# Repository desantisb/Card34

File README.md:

# Card34
A compact split keyboard with 34 keys and bluetooth connection

Initial design is done starting from Sweep2.1 half design.

wiring is kept same as the sweep so Sweep compatible firmware should be also compatible with the Card34.

Card34 is supposed to work only through Bluetooth so TRRS connection has not been included.

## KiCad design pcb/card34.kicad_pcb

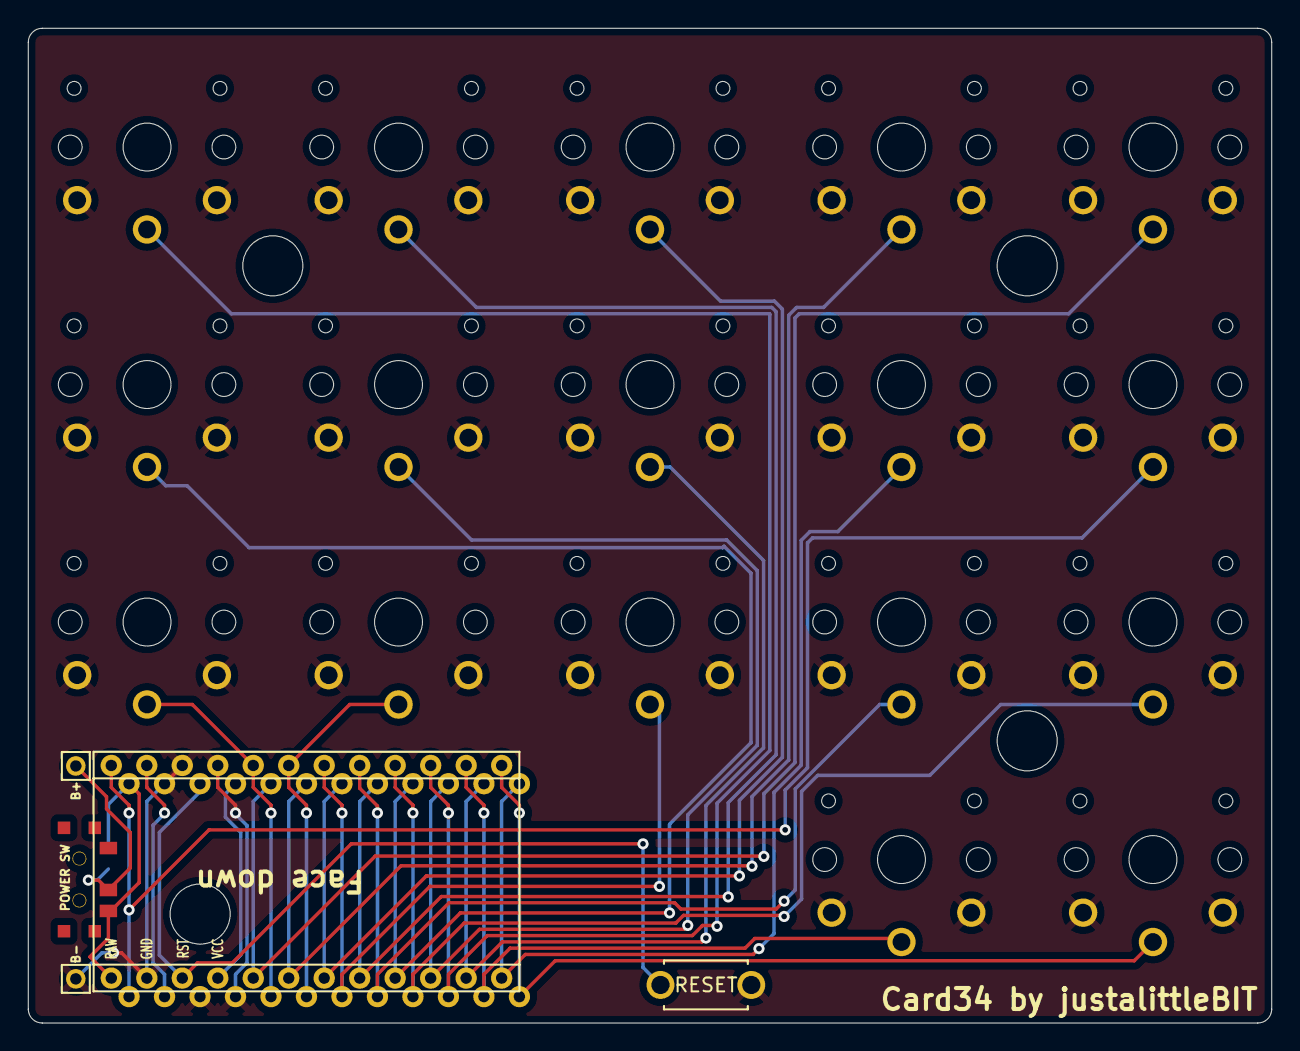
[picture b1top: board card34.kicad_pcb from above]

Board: 2 copper layers, 89.0 x 71.2 mm, 23 parts (1 on the bottom side), 21 nets.

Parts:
B+: MountingHole_Pad; 1pin_conn
B-: MountingHole_Pad; 1pin_conn
POWER SW: SW_SPDT; SPDT_C128955
RSW1: SW_Push; ResetSW
SW2, SW3, SW4, SW5, SW6, SW8, SW9, SW10, SW11, SW12, SW14, SW15, SW16, SW17, SW18, SW20, SW21: SW_Push; SW_PG1350_rev_DPB
SW2#2: SW_SPDT; SPDT_C128955r
U1: ProMicro-kbd; ProMicro_v2

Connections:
BT+_r: B+.1, POWER SW.2, SW2#2.2
Switch1: SW2.1, U1.10
Switch2: SW3.1, U1.17
Switch3: SW4.1, U1.18
Switch4: SW5.1, U1.19
Switch5: SW6.1, U1.20
Switch6: SW8.1, U1.16
Switch7: SW9.1, U1.15
Switch8: SW10.1, U1.14
Switch9: SW11.1, U1.13
Switch10: SW12.1, U1.1
Switch11: SW14.1, U1.5
Switch12: SW15.1, U1.6
Switch13: SW16.1, U1.7
Switch14: SW17.1, U1.8
Switch15: SW18.1, U1.9
Switch16: SW21.1, U1.11
Switch17: SW20.1, U1.12
gnd: B-.1, RSW1.1, SW2.2, SW3.2, SW4.2, SW5.2, SW6.2, SW8.2, SW9.2, SW10.2, SW11.2, SW12.2, SW14.2, SW15.2, SW16.2, SW17.2, SW18.2, SW20.2, SW21.2, U1.3, U1.4, U1.23
raw: POWER SW.3, SW2#2.3, U1.24
reset: RSW1.2, U1.22

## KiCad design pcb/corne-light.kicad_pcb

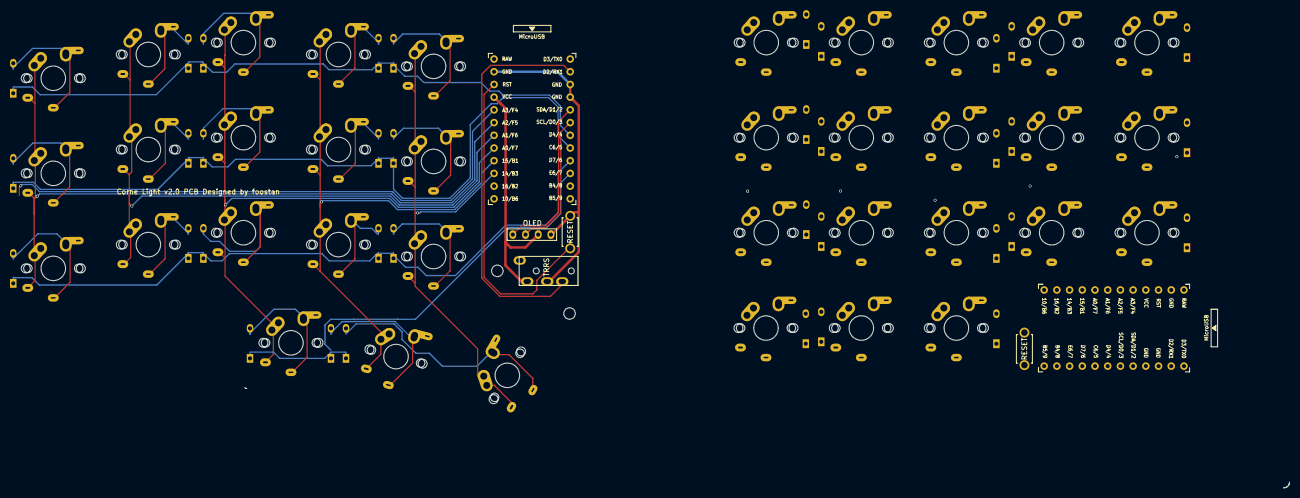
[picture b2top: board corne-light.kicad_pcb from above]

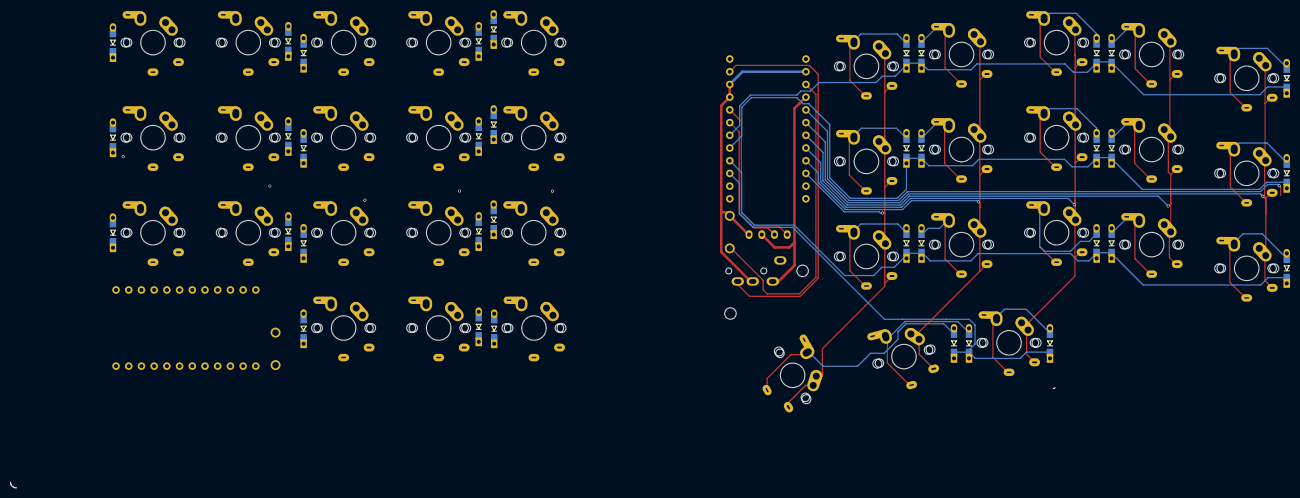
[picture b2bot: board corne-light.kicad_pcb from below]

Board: 2 copper layers, 80 parts (38 on the bottom side), 62 nets.

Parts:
D2, D3, D4, D5, D6, D8, D9, D10, D11, D12, D14, D15, D16, D17, D18, D19, D20, D21, D23, D24, D25, D26, D27, D29, D30, D31, D32, D33, D35, D36, D37, D38, D39, D40, D41, D42: D; D3_TH_SMD_v2
J1: MJ-4PP-9; MJ-4PP-9_1side
J2: OLED; OLED_1side
RSW1, RSW2: SW_PUSH; ResetSW_1side
Ref**: Val**; thread_m2
Ref**#2: Val**; thread_m2
SW2, SW3, SW4, SW5, SW6, SW8, SW9, SW10, SW11, SW12, SW14, SW15, SW16, SW17, SW18, SW19, SW20, SW23, SW24, SW25, SW26, SW27, SW29, SW30, SW31, SW32, SW33, SW35, SW36, SW37, SW38, SW39, SW40, SW41, SW42: SW_PUSH; keyswitch_cherrymx_alps_choc12_1u
SW21: SW_PUSH; keyswitch_cherrymx_alps_choc12_1.5u
U1, U2: ProMicro; ProMicro_v3

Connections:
GND: J1.C, J2.4, RSW1.2, U1.3, U1.4, U1.23
GNDA: RSW2.2, U2.3, U2.4, U2.23
unnamed: D2.2, SW2.2
unnamed: D3.2, SW3.2
unnamed: D4.2, SW4.2
unnamed: D5.2, SW5.2
unnamed: D6.2, SW6.2
unnamed: D8.2, SW8.2
unnamed: D9.2, SW9.2
unnamed: D10.2, SW10.2
unnamed: D11.2, SW11.2
unnamed: D12.2, SW12.2
unnamed: D14.2, SW14.2
unnamed: D15.2, SW15.2
unnamed: D16.2, SW16.2
unnamed: D17.2, SW17.2
unnamed: D18.2, SW18.2
unnamed: D19.2, SW19.2
unnamed: D20.2, SW20.2
unnamed: D21.2, SW21.2
unnamed: D23.2, SW23.2
unnamed: D24.2, SW24.2
unnamed: D25.2, SW25.2
unnamed: D26.2, SW26.2
unnamed: D27.2, SW27.2
unnamed: D29.2, SW29.2
unnamed: D30.2, SW30.2
unnamed: D31.2, SW31.2
unnamed: D32.2, SW32.2
unnamed: D33.2, SW33.2
unnamed: D35.2, SW35.2
unnamed: D36.2, SW36.2
unnamed: D37.2, SW37.2
unnamed: D38.2, SW38.2
unnamed: D39.2, SW39.2
unnamed: D40.2, SW40.2
unnamed: D41.2, SW41.2
unnamed: D42.2, SW42.2
SCL: J2.2, U1.6
SDA: J2.1, U1.5
VCC: J1.D, J2.3, U1.21
col1: SW2.1, SW8.1, SW14.1, U1.19
col1_r: SW23.1, SW29.1, SW35.1, U2.19
col2: SW3.1, SW9.1, SW15.1, U1.18
col2_r: SW24.1, SW30.1, SW36.1, U2.18
col3: SW4.1, SW10.1, SW16.1, SW19.1, U1.17
col3_r: SW25.1, SW31.1, SW37.1, SW40.1, U2.17
col4: SW5.1, SW11.1, SW17.1, SW20.1, U1.16
col4_r: SW26.1, SW32.1, SW38.1, SW41.1, U2.16
col5: SW6.1, SW12.1, SW18.1, SW21.1, U1.15
col5_r: SW27.1, SW33.1, SW39.1, SW42.1, U2.15
data: J1.B, U1.2
reset: RSW1.1, U1.22
reset_r: RSW2.1, U2.22
row0: D2.1, D3.1, D4.1, D5.1, D6.1, U1.7
row0_r: D23.1, D24.1, D25.1, D26.1, D27.1, U2.7
row1: D8.1, D9.1, D10.1, D11.1, D12.1, U1.8
row1_r: D29.1, D30.1, D31.1, D32.1, D33.1, U2.8
row2: D14.1, D15.1, D16.1, D17.1, D18.1, U1.9
row2_r: D35.1, D36.1, D37.1, D38.1, D39.1, U2.9
row3: D19.1, D20.1, D21.1, U1.10
row3_r: D40.1, D41.1, D42.1, U2.10

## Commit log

2022-04-06 first issue
    pcb is obtained rearranging the sweep2 half
2022-04-06 folders rearranged
